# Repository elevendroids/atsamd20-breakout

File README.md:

# ATSAMD2x (SAM D2x) Breakout Board (Rev. A)

Small breakout board designed for the [SAM D20](http://ww1.microchip.com/downloads/en/DeviceDoc/SAM_D20_%20Family_Datasheet_DS60001504C.pdf) and [SAM D21](http://ww1.microchip.com/downloads/en/DeviceDoc/SAM_D21_DA1_Family_DataSheet_DS40001882F.pdf) ARM Cortex-M0+ microcontrollers from Microchip

## Features

- minimal subset of components, no power regulation etc.
- optional external main and real-time crystals - if not used, their GPIO pins can be connected to the user header by soldering relevant 0R resistors (see schematic)
- one buffered user LED, connected to the header - no reserved GPIO
- reset button
- standard 0.05" pitch SWD programming header, SWD signals also present on the pin headers

Designed in KiCad 5.1.6

Schematic: [PDF](docs/atsamd20-breakout.pdf)

License: [CC BY-SA 4.0](https://creativecommons.org/licenses/by-sa/4.0/)

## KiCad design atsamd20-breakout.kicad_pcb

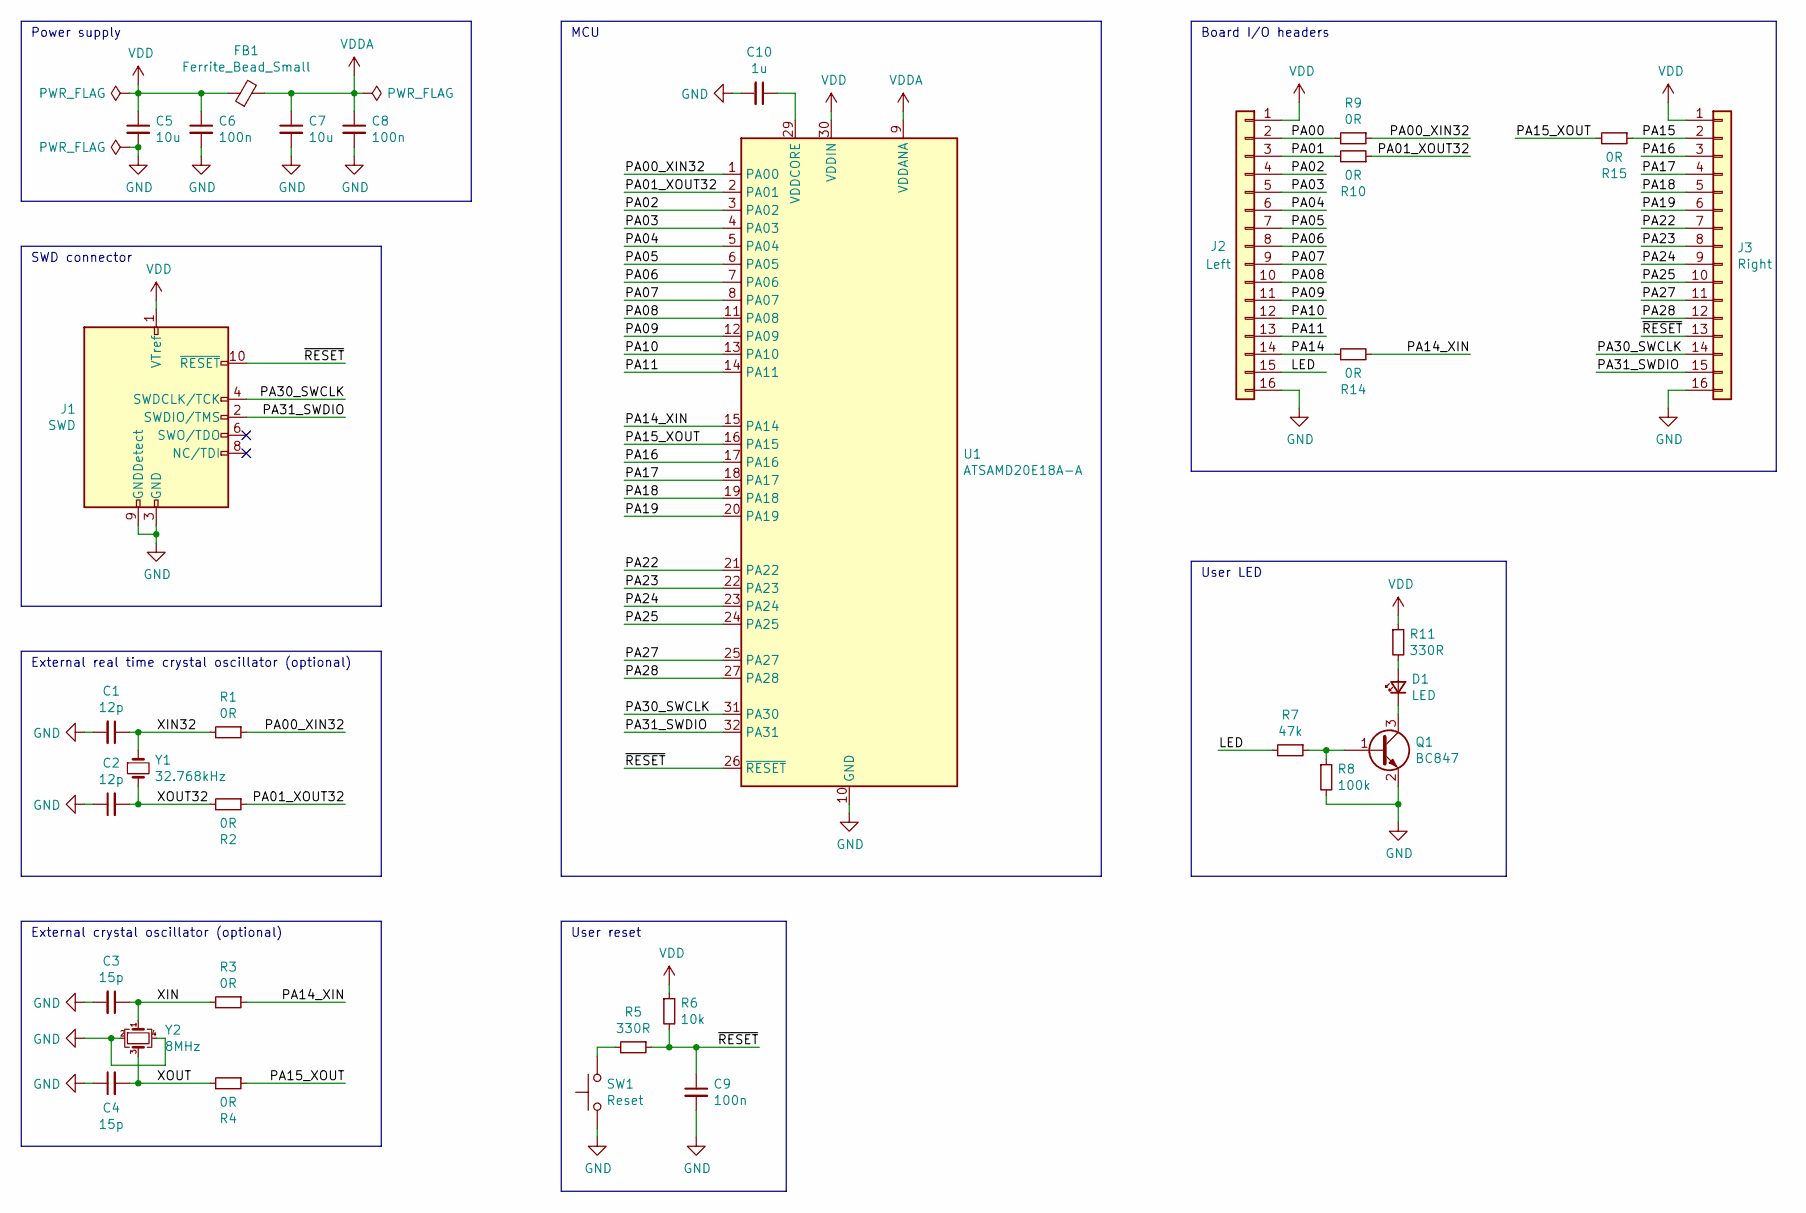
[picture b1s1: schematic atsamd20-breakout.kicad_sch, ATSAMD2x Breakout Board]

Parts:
C1, C2: 12p; C_0603_1608Metric
C3, C4: 15p; C_0603_1608Metric
C5, C7: 10u; C_0805_2012Metric
C6, C8, C9: 100n; C_0603_1608Metric
C10: 1u; C_0603_1608Metric
D1: LED; LED_0805_2012Metric
FB1: Ferrite_Bead_Small; L_0603_1608Metric
J1: SWD; PinHeader_2x05_P1.27mm_Vertical_SMD
J2: Left; PinHeader_1x16_P2.54mm_Vertical
J3: Right; PinHeader_1x16_P2.54mm_Vertical
Q1: BC847; SOT-23
R1, R2, R3, R4, R9, R10, R14, R15: 0R; R_0603_1608Metric
R5, R11: 330R; R_0603_1608Metric
R6: 10k; R_0603_1608Metric
R7: 47k; R_0603_1608Metric
R8: 100k; R_0603_1608Metric
SW1: Reset; SW_SPST_CK_RS282G05A3
U1: ATSAMD20E18A-A; TQFP-32_7x7mm_P0.8mm
Y1: 32.768kHz; Crystal_SMD_3215-2Pin_3.2x1.5mm
Y2: 8MHz; Crystal_SMD_5032-4Pin_5.0x3.2mm

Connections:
/LED: J2.15, R7.2
/PA00: J2.2, R9.2
/PA00_XIN32: R1.1, R9.1, U1.1 (PA00)
/PA01: J2.3, R10.2
/PA01_XOUT32: R2.1, R10.1, U1.2 (PA01)
/PA02: J2.4, U1.3 (PA02)
/PA03: J2.5, U1.4 (PA03)
/PA04: J2.6, U1.5 (PA04)
/PA05: J2.7, U1.6 (PA05)
/PA06: J2.8, U1.7 (PA06)
/PA07: J2.9, U1.8 (PA07)
/PA08: J2.10, U1.11 (PA08)
/PA09: J2.11, U1.12 (PA09)
/PA10: J2.12, U1.13 (PA10)
/PA11: J2.13, U1.14 (PA11)
/PA14: J2.14, R14.1
/PA14_XIN: R3.1, R14.2, U1.15 (PA14)
/PA15: J3.2, R15.1
/PA15_XOUT: R4.1, R15.2, U1.16 (PA15)
/PA16: J3.3, U1.17 (PA16)
/PA17: J3.4, U1.18 (PA17)
/PA18: J3.5, U1.19 (PA18)
/PA19: J3.6, U1.20 (PA19)
/PA22: J3.7, U1.21 (PA22)
/PA23: J3.8, U1.22 (PA23)
/PA24: J3.9, U1.23 (PA24)
/PA25: J3.10, U1.24 (PA25)
/PA27: J3.11, U1.25 (PA27)
/PA28: J3.12, U1.27 (PA28)
/PA30_SWCLK: J1.4 (SWDCLK/TCK), J3.14, U1.31 (PA30)
/PA31_SWDIO: J1.2 (SWDIO/TMS), J3.15, U1.32 (PA31)
/XIN: C3.1, R3.2, Y2.1
/XIN32: C1.1, R1.2, Y1.1
/XOUT: C4.2, R4.2, Y2.3
/XOUT32: C2.2, R2.2, Y1.2
/~RESET: C9.1, J1.10 (~RESET), J3.13, R5.1, R6.2, U1.26 (~RESET)
GND: C1.2, C2.1, C3.2, C4.1, C5.2, C6.2, C7.2, C8.2, C9.2, C10.2, J1.3 (GND), J1.5 (GND), J1.9 (GNDDetect), J2.16, J3.16, Q1.2 (E), R8.2, SW1.1, U1.10 (GND), U1.28 (GND), Y2.2, Y2.4
unnamed: C10.1, U1.29 (VDDCORE)
unnamed: D1.1 (K), Q1.3 (C)
unnamed: D1.2 (A), R11.2
unnamed: Q1.1 (B), R7.1, R8.1
unnamed: R5.2, SW1.2
VDD: C5.1, C6.1, FB1.1, J1.1 (VTref), J2.1, J3.1, R6.1, R11.1, U1.30 (VDDIN)
VDDA: C7.1, C8.1, FB1.2, U1.9 (VDDANA)

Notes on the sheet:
SWD connector
User reset
External crystal oscillator (optional)
External real time crystal oscillator (optional)
Board I/O headers
MCU
User LED
Power supply

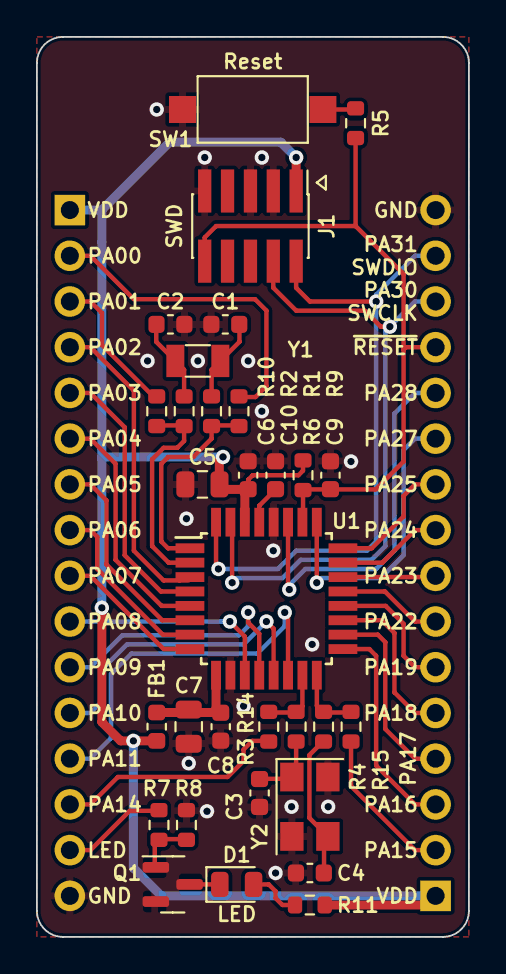
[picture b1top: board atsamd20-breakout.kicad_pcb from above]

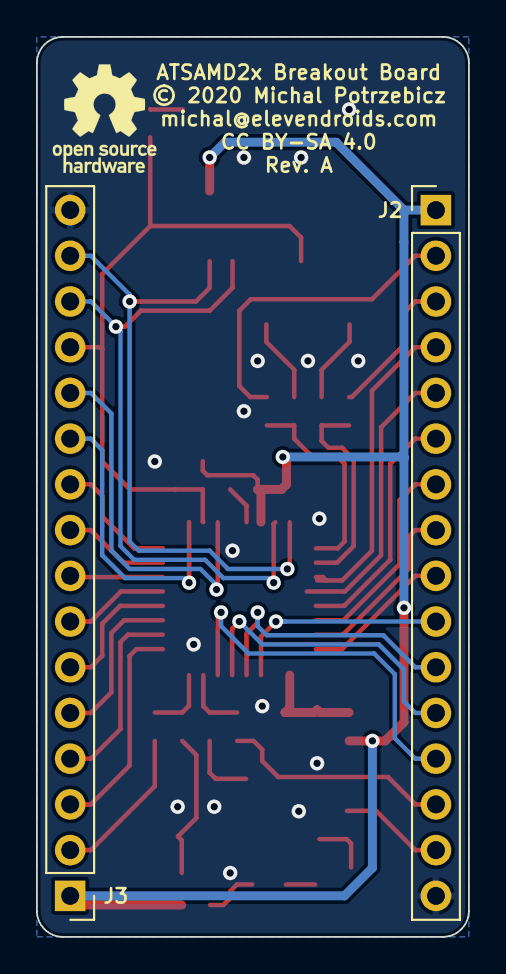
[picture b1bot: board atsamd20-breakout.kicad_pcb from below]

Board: 2 copper layers, 24.0 x 50.0 mm, 33 parts (2 on the bottom side), 44 nets.

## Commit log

2020-08-02 Initial commit, schematic completed
2020-08-02 Replaced LED1 pin with RESET, removed LED1 circuit
2020-08-02 Fixed net names
2020-08-03 Fixed SWD connector wire labels
2020-08-16 Finished (hopefully) the layout for the Rev. A
2020-08-17 Added readme, license and pcb render
2020-08-29 Added pin 1 indicator for the SWD connector
2020-09-14 Added photo of the first prototype from OSHPark
2020-09-14 Added interactive BOM
2022-04-02 Project upgrade to KiCad 6

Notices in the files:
atsamd20-breakout.kicad_pcb:
© 2020 Michal Potrzebicz
CC BY-SA 4.0
